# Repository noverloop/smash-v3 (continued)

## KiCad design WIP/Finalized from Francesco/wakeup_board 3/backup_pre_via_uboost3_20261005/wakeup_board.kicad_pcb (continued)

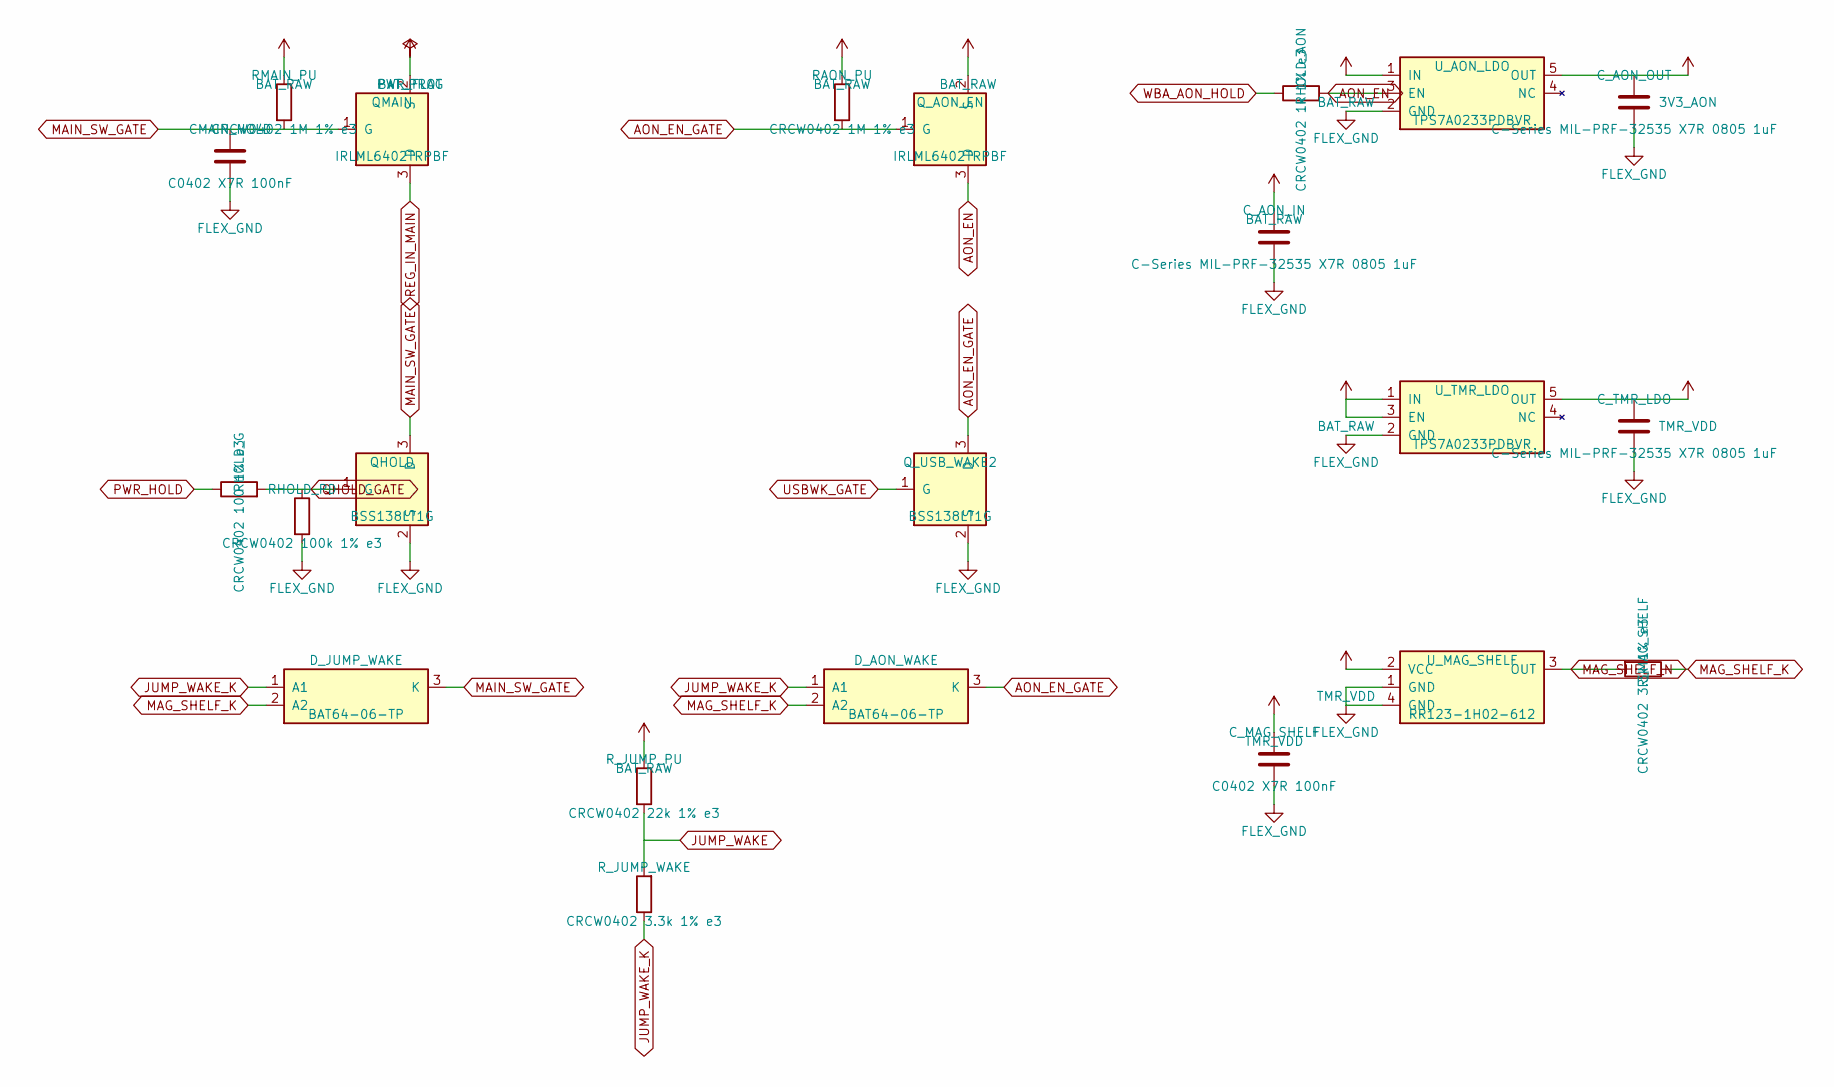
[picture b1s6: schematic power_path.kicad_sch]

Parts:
CMAIN_HOLD: C0402 X7R 100nF; Capacitor_SMD_C_0402_1005Metric
C_AON_IN: C-Series MIL-PRF-32535 X7R 0805 1uF; Capacitor_SMD_C_0805_2012Metric
C_AON_OUT: C-Series MIL-PRF-32535 X7R 0805 1uF; Capacitor_SMD_C_0805_2012Metric
C_MAG_SHELF: C0402 X7R 100nF; Capacitor_SMD_C_0402_1005Metric
C_TMR_LDO: C-Series MIL-PRF-32535 X7R 0805 1uF; Capacitor_SMD_C_0805_2012Metric
D_AON_WAKE: BAT64-06-TP; SOT95P237X125-3N
D_JUMP_WAKE: BAT64-06-TP; SOT95P237X125-3N
QHOLD: BSS138LT1G; SOT96P237X111-3N
QMAIN: IRLML6402TRPBF; SOT95P237X112-3N
Q_AON_EN: IRLML6402TRPBF; SOT95P237X112-3N
Q_USB_WAKE2: BSS138LT1G; SOT96P237X111-3N
RAON_PU: CRCW0402 1M 1% e3; Resistor_SMD_R_0402_1005Metric
RHOLD_AON: CRCW0402 1k 1% e3; Resistor_SMD_R_0402_1005Metric
RHOLD_G: CRCW0402 100 1% e3; Resistor_SMD_R_0402_1005Metric
RHOLD_PD: CRCW0402 100k 1% e3; Resistor_SMD_R_0402_1005Metric
RMAIN_PU: CRCW0402 1M 1% e3; Resistor_SMD_R_0402_1005Metric
R_JUMP_PU: CRCW0402 22k 1% e3; Resistor_SMD_R_0402_1005Metric
R_JUMP_WAKE: CRCW0402 3.3k 1% e3; Resistor_SMD_R_0402_1005Metric
R_MAG_SHELF: CRCW0402 3.3k 1% e3; Resistor_SMD_R_0402_1005Metric
U_AON_LDO: TPS7A0233PDBVR; SOT95P280X145-5N
U_MAG_SHELF: RR123-1H02-612
U_TMR_LDO: TPS7A0233PDBVR; SOT95P280X145-5N

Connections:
3V3_AON: C_AON_OUT.1, U_AON_LDO.5 (OUT); also elsewhere on the board
AON_EN: Q_AON_EN.3 (D), RHOLD_AON.2, U_AON_LDO.3 (EN)
AON_EN_GATE: D_AON_WAKE.3 (K), Q_AON_EN.1 (G), Q_USB_WAKE2.3 (D), RAON_PU.2
BAT_PROT: QMAIN.2 (S); also elsewhere on the board
BAT_RAW: C_AON_IN.1, Q_AON_EN.2 (S), RAON_PU.1, RMAIN_PU.1, R_JUMP_PU.1, U_AON_LDO.1 (IN), U_TMR_LDO.1 (IN), U_TMR_LDO.3 (EN); also elsewhere on the board
FLEX_GND: CMAIN_HOLD.2, C_AON_IN.2, C_AON_OUT.2, C_MAG_SHELF.2, C_TMR_LDO.2, QHOLD.2 (S), Q_USB_WAKE2.2 (S), RHOLD_PD.2, U_AON_LDO.2 (GND), U_MAG_SHELF.1 (GND), U_MAG_SHELF.4 (GND), U_TMR_LDO.2 (GND); also elsewhere on the board
JUMP_WAKE_K: D_AON_WAKE.1 (A1), D_JUMP_WAKE.1 (A1), R_JUMP_WAKE.1
MAG_SHELF_K: D_AON_WAKE.2 (A2), D_JUMP_WAKE.2 (A2), R_MAG_SHELF.1
MAG_SHELF_N: R_MAG_SHELF.2, U_MAG_SHELF.3 (OUT)
MAIN_SW_GATE: CMAIN_HOLD.1, D_JUMP_WAKE.3 (K), QHOLD.3 (D), QMAIN.1 (G), RMAIN_PU.2; also elsewhere on the board
PWR_HOLD: RHOLD_G.1; also elsewhere on the board
QHOLD_GATE: QHOLD.1 (G), RHOLD_G.2, RHOLD_PD.1
REG_IN_MAIN: QMAIN.3 (D); also elsewhere on the board
TMR_VDD: C_MAG_SHELF.1, C_TMR_LDO.1, U_MAG_SHELF.2 (VCC), U_TMR_LDO.5 (OUT)
USBWK_GATE: Q_USB_WAKE2.1 (G); also elsewhere on the board
WBA_AON_HOLD: RHOLD_AON.1; also elsewhere on the board

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
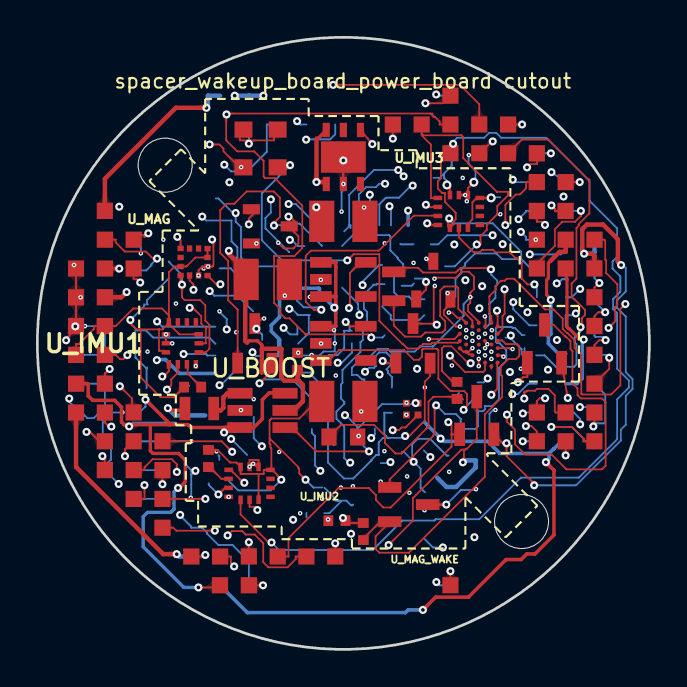
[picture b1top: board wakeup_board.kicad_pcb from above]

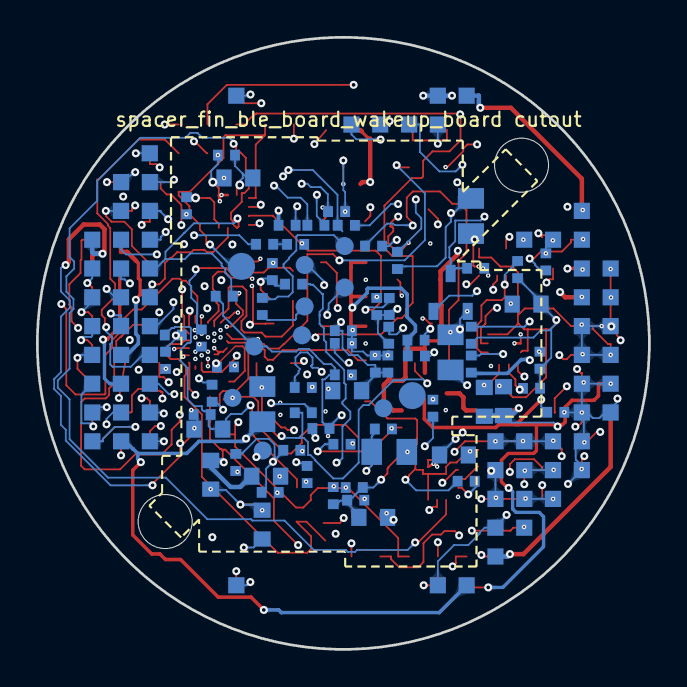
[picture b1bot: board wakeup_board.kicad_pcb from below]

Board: 14 copper layers, 34.0 x 34.0 mm, 111 parts (80 on the bottom side), 85 nets.

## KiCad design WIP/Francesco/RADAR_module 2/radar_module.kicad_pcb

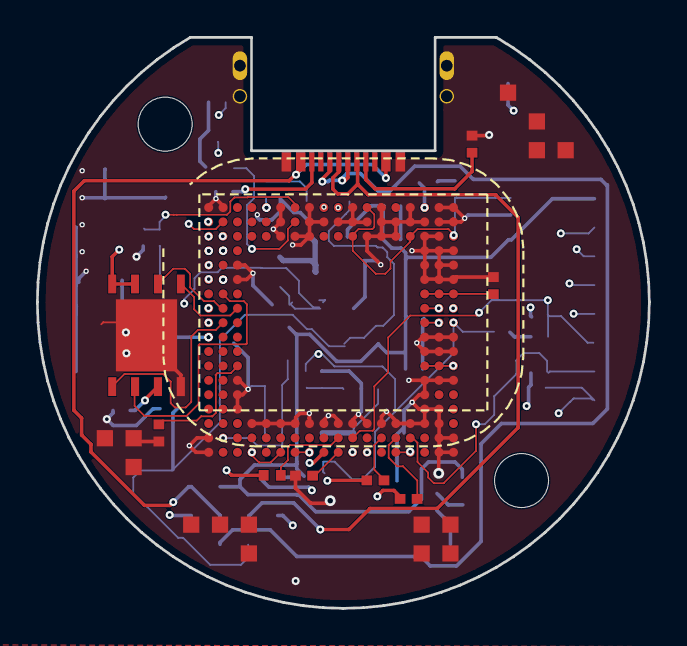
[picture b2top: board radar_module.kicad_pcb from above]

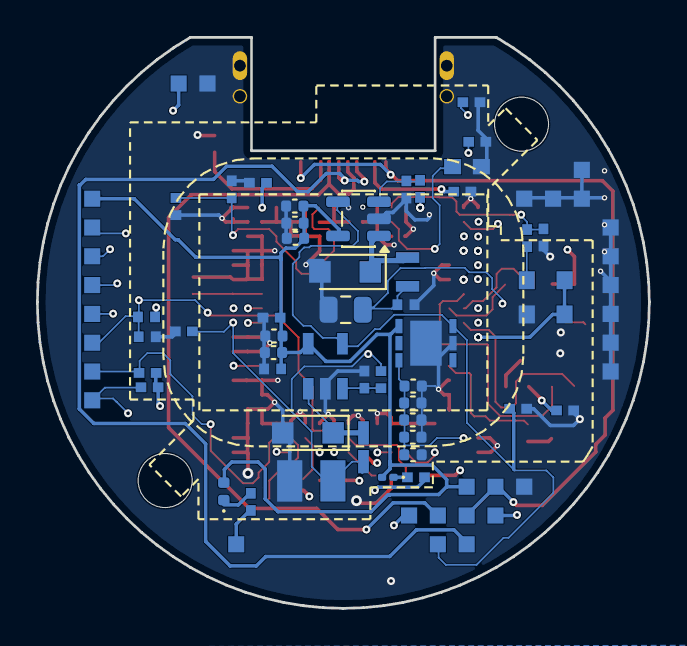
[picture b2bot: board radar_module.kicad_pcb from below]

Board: 20 copper layers, 34.0 x 31.7 mm, 59 parts (48 on the bottom side), 43 nets.

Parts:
C_AWR_1V2_1: T491T 22uF (3528-12 thinnest variant); C_0805_2012Metric
C_AWR_1V2_2, C_AWR_1V3_2, C_AWR_1V8_2, C_AWR_14APLL, C_AWR_14SYNTH: C0402 X7R 100nF; C_0402_1005Metric
C_AWR_1V3_1: T491T 22uF (3528-12 thinnest variant); CP_EIA-3528-12_Kemet-T
C_AWR_1V8_1_1, C_AWR_1V8_1_2, C_AWR_1V8_1_3, C_AWR_1V8_1_4, C_AWR_1V8_1_5: C-Series MIL-PRF-32535 X7R 0603 2.2uF; C_0402_1005Metric
C_AWR_BUCK_IN1_1, C_AWR_BUCK_IN1_2, C_AWR_BUCK_IN1_3, C_AWR_BUCK_IN1_4, C_AWR_BUCK_IN1_5: C-Series MIL-PRF-32535 X7R 0603 2.2uF; C_0402_1005Metric
C_AWR_BUCK_IN2: C0402 X7R 100nF; C_0402_1005Metric
C_AWR_CLKM: SQCSVA 100pF; C_0603_1608Metric
C_AWR_FLASH_VCC: C0402 X7R 100nF; C_0402_1005Metric
C_AWR_NRST: C0402 X7R 100nF; C_0402_1005Metric
C_AWR_OSC_VDD: C0402 X7R 100nF; C_0402_1005Metric
C_AWR_VBGAP: C0402 X7R 100nF; C_0402_1005Metric
C_AWR_VOUT_PA: C0402 X7R 100nF; C_0402_1005Metric
C_NOSE_LED: C0402 X7R 100nF; C_0402_1005Metric
D_AWR_BUCK12, D_AWR_BUCK13: MBRS340T3G; Nexperia_CFP3_SOD-123W
D_NOSE_G: LTST-C190GKT; LED_0402_1005Metric
D_NOSE_R: LTST-C190KRKT; LED_0201_0603Metric
J_USB_C: UJ20-C-H-G-MSMT-1A-P16-TR-67; SAMESKY_UJ20-C-H-G-MSMT-1A-P16-TR-67
J_radar_module_spacer_radar_module_nose_cap: LGA_lands; J_radar_module_spacer_radar_module_nose_cap
L_AWR_BUCK12, L_AWR_BUCK13: TMS201210ALM-2R2MTAA; L_2012_2.0x1.25mm
P_radar_module_spacer_companion_compute_radar_module: LGA_lands; P_radar_module_spacer_companion_compute_radar_module
R_AWR12_FB1, R_AWR12_FB2, R_AWR13_FB2: CRCW0402 100k 1% e3; R_0402_1005Metric
R_AWR13_FB1: CRCW0402 118k 1% e3; R_0402_1005Metric
R_AWR_CLK_SER: CRCW0402 330 1% e3; R_0402_1005Metric
R_AWR_CLK_SH: CRCW0402 390 1% e3; R_0402_1005Metric
R_AWR_DRDY_PU: CRCW0402 10k 1% e3; R_0402_1005Metric
R_AWR_FAULT_PU: CRCW0402 100k 1% e3; R_0402_1005Metric
R_AWR_NERRIN_PU: CRCW0402 10k 1% e3; R_0402_1005Metric
R_AWR_NRST: CRCW0402 10k 1% e3; R_0402_1005Metric
R_AWR_SOP0, R_AWR_SOP1, R_AWR_SOP2: CRCW0402 10k 1% e3; R_0402_1005Metric
R_AWR_WARMRST_PU: CRCW0402 10k 1% e3; R_0402_1005Metric
R_NOSE_LED_G: CRCW0402 330 1% e3; R_0402_1005Metric
R_NOSE_LED_R: CRCW0402 330 1% e3; R_0402_1005Metric
R_RADAR_EN_PD: CRCW0402 100k 1% e3; R_0402_1005Metric
R_USB_CC1, R_USB_CC2: CRCW0402 5.1k 1% e3; R_0402_1005Metric
U_AWR: AWR1843ARBGALPQ1; BGA180C80P18X18_1500X1500X96
U_AWR_BUCK12: LMR10510XMFE/NOPB; SOT-23-5
U_AWR_BUCK13: LMR10510XMFE/NOPB; SOT95P280X145-5N
U_AWR_FLASH: SST26VF080A-104I/MF; SON127P600X500X80-9N-D
U_AWR_LDO18: LDL112PV18R; SON95P300X300X100-7N-D
Y_AWR_HSE: DSC1001CI5-040.0000; DSC1001CI50080000

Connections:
AWR_1V2: C_AWR_1V2_1.1, C_AWR_1V2_2.1, L_AWR_BUCK12.2, R_AWR12_FB1.1, U_AWR.A5, U_AWR.C1, U_AWR.E1, U_AWR.J1, U_AWR.V4, U_AWR.V6, U_AWR.V7, U_AWR.V8, U_AWR.V12, U_AWR.V14, U_AWR.V15
AWR_1V2_FB: R_AWR12_FB1.2, R_AWR12_FB2.1, U_AWR_BUCK12.3
AWR_1V2_SW: D_AWR_BUCK12.1, L_AWR_BUCK12.1, U_AWR_BUCK12.1
AWR_1V3: C_AWR_1V3_1.1, C_AWR_1V3_2.1, L_AWR_BUCK13.2, R_AWR13_FB1.1, U_AWR.H16, U_AWR.H17, U_AWR.H18, U_AWR.J16, U_AWR.J17, U_AWR.J18
AWR_1V3_FB: R_AWR13_FB1.2, R_AWR13_FB2.1, U_AWR_BUCK13.3
AWR_1V3_SW: D_AWR_BUCK13.1, L_AWR_BUCK13.1, U_AWR_BUCK13.1
AWR_1V8: C_AWR_1V8_1_1.1, C_AWR_1V8_1_2.1, C_AWR_1V8_1_3.1, C_AWR_1V8_1_4.1, C_AWR_1V8_1_5.1, C_AWR_1V8_2.1, C_AWR_OSC_VDD.1, U_AWR.A12, U_AWR.B1, U_AWR.C11, U_AWR.C15, U_AWR.C18, U_AWR.F1, U_AWR.K1, U_AWR.M16, U_AWR.M17, U_AWR.M18, U_AWR.U2, U_AWR.V11, U_AWR_LDO18.4, Y_AWR_HSE.1, Y_AWR_HSE.4
AWR_CLKM: C_AWR_CLKM.1, U_AWR.B7
AWR_CLKREF: R_AWR_CLK_SER.2, R_AWR_CLK_SH.1, U_AWR.A7
AWR_DRDY: P_radar_module_spacer_companion_compute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.1, R_AWR_DRDY_PU.2, U_AWR.B2
AWR_FAULT: P_radar_module_spacer_companion_compute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.2, R_AWR_FAULT_PU.2, U_AWR.U15
AWR_NERR_IN: R_AWR_NERRIN_PU.2, U_AWR.U14
AWR_NRESET: C_AWR_NRST.1, P_radar_module_spacer_companion_compute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.3, R_AWR_NRST.2, U_AWR.U11
AWR_OSC_OUT: R_AWR_CLK_SER.1, Y_AWR_HSE.3
AWR_QSPI_CLK: U_AWR.H2, U_AWR_FLASH.6
AWR_QSPI_CS: U_AWR.J2, U_AWR_FLASH.1
AWR_QSPI_SI: U_AWR.H3, U_AWR_FLASH.5
AWR_QSPI_SO: U_AWR.G2, U_AWR_FLASH.2
AWR_SOP0: R_AWR_SOP0.2, U_AWR.U10
AWR_SOP1: R_AWR_SOP1.1, U_AWR.M3
AWR_SOP2: R_AWR_SOP2.1, U_AWR.V10
AWR_SPI_CLK: P_radar_module_spacer_companion_compute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.4, U_AWR.D2
AWR_SPI_CS: P_radar_module_spacer_companion_compute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.5, U_AWR.C2
AWR_SPI_MISO: P_radar_module_spacer_companion_compute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.6, U_AWR.D1
AWR_SPI_MOSI: P_radar_module_spacer_companion_compute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.7, U_AWR.F2
AWR_VOUT_14APLL: C_AWR_14APLL.1, U_AWR.A10
AWR_VOUT_14SYNTH: C_AWR_14SYNTH.1, U_AWR.A9
AWR_VOUT_PA: C_AWR_VOUT_PA.1, U_AWR.G16, U_AWR.G17, U_AWR.G18
AWR_WARM_RST: R_AWR_WARMRST_PU.2, U_AWR.U13
BAT_PROT: C_AWR_BUCK_IN1_1.1, C_AWR_BUCK_IN1_2.1, C_AWR_BUCK_IN1_3.1, C_AWR_BUCK_IN1_4.1, C_AWR_BUCK_IN1_5.1, C_AWR_BUCK_IN2.1, C_NOSE_LED.1, D_NOSE_G.2, D_NOSE_R.2, P_radar_module_spacer_companion_compute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.8, P_radar_module_spacer_companion_compute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.17, U_AWR_BUCK12.5, U_AWR_BUCK13.5, U_AWR_LDO18.6
COMP_3V3: C_AWR_FLASH_VCC.1, P_radar_module_spacer_companion_compute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.9, P_radar_module_spacer_companion_compute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.18, R_AWR_DRDY_PU.1, R_AWR_FAULT_PU.1, R_AWR_NERRIN_PU.1, R_AWR_NRST.1, R_AWR_SOP0.1, R_AWR_WARMRST_PU.1, U_AWR.H1, U_AWR.V9, U_AWR_FLASH.3, U_AWR_FLASH.7, U_AWR_FLASH.8
FLEX_GND: C_AWR_1V2_1.2, C_AWR_1V2_2.2, C_AWR_1V3_1.2, C_AWR_1V3_2.2, C_AWR_1V8_1_1.2, C_AWR_1V8_1_2.2, C_AWR_1V8_1_3.2, C_AWR_1V8_1_4.2, C_AWR_1V8_1_5.2, C_AWR_1V8_2.2, C_AWR_14APLL.2, C_AWR_14SYNTH.2, C_AWR_BUCK_IN1_1.2, C_AWR_BUCK_IN1_2.2, C_AWR_BUCK_IN1_3.2, C_AWR_BUCK_IN1_4.2, C_AWR_BUCK_IN1_5.2, C_AWR_BUCK_IN2.2, C_AWR_CLKM.2, C_AWR_FLASH_VCC.2, C_AWR_NRST.2, C_AWR_OSC_VDD.2, C_AWR_VBGAP.2, C_AWR_VOUT_PA.2, C_NOSE_LED.2, D_AWR_BUCK12.2, D_AWR_BUCK13.2, J_USB_C.A1_B12, J_USB_C.B1_A12, J_USB_C.SH1, J_USB_C.SH2, J_USB_C.SH3, J_USB_C.SH4, J_radar_module_spacer_radar_module_nose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.1, J_radar_module_spacer_radar_module_nose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.2, J_radar_module_spacer_radar_module_nose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.3, J_radar_module_spacer_radar_module_nose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.4, J_radar_module_spacer_radar_module_nose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.5, J_radar_module_spacer_radar_module_nose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.6, J_radar_module_spacer_radar_module_nose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.7, J_radar_module_spacer_radar_module_nose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.8, J_radar_module_spacer_radar_module_nose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.9, J_radar_module_spacer_radar_module_nose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.10, J_radar_module_spacer_radar_module_nose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.11, J_radar_module_spacer_radar_module_nose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.12, J_radar_module_spacer_radar_module_nose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.13, J_radar_module_spacer_radar_module_nose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.14, J_radar_module_spacer_radar_module_nose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.15, P_radar_module_spacer_companion_compute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.10, P_radar_module_spacer_companion_compute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.20, P_radar_module_spacer_companion_compute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.21, P_radar_module_spacer_companion_compute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.22, P_radar_module_spacer_companion_compute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.23, P_radar_module_spacer_companion_compute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.24, P_radar_module_spacer_companion_compute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.25, P_radar_module_spacer_companion_compute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.26, P_radar_module_spacer_companion_compute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.27, P_radar_module_spacer_companion_compute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.28, P_radar_module_spacer_companion_compute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.29, P_radar_module_spacer_companion_compute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.30, R_AWR12_FB2.2, R_AWR13_FB2.2, R_AWR_CLK_SH.2, R_AWR_SOP1.2, R_AWR_SOP2.2, R_RADAR_EN_PD.2, R_USB_CC1.2, R_USB_CC2.2, U_AWR.A1, U_AWR.A2, U_AWR.A6, U_AWR.A8, U_AWR.A11, U_AWR.A13, U_AWR.A15, U_AWR.A17, U_AWR.A18, U_AWR.B6, U_AWR.B8, U_AWR.B9, U_AWR.B10, U_AWR.B11, U_AWR.B12, U_AWR.B13, U_AWR.B14, U_AWR.B15, U_AWR.B16, U_AWR.B17, U_AWR.B18, U_AWR.C6, U_AWR.C7, U_AWR.C8, U_AWR.C12, U_AWR.C13, U_AWR.C14, U_AWR.C16, U_AWR.C17, U_AWR.D16, U_AWR.D17, U_AWR.D18, U_AWR.E3, U_AWR.E16, U_AWR.E17, U_AWR.E18, U_AWR.F3, U_AWR.F16, U_AWR.F17, U_AWR.F18, U_AWR.K16, U_AWR.K17, U_AWR.K18, U_AWR.L16, U_AWR.L17, U_AWR.L18, U_AWR.N3, U_AWR.N16, U_AWR.N17, U_AWR.N18, U_AWR.P3, U_AWR.P16, U_AWR.R3, U_AWR.R16, U_AWR.R17, U_AWR.T4, U_AWR.T5, U_AWR.T6, U_AWR.T7, U_AWR.T8, U_AWR.T9, U_AWR.T10, U_AWR.T11, U_AWR.T12, U_AWR.T13, U_AWR.T14, U_AWR.T15, U_AWR.T16, U_AWR.T17, U_AWR.U1, U_AWR.U17, U_AWR.U18, U_AWR.V1, U_AWR.V17, U_AWR.V18, U_AWR_BUCK12.2, U_AWR_BUCK13.2, U_AWR_FLASH.4, U_AWR_FLASH.9, U_AWR_LDO18.2, U_AWR_LDO18.7, Y_AWR_HSE.2
NOSE_LED_G: P_radar_module_spacer_companion_compute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.11, R_NOSE_LED_G.2
NOSE_LED_G_K: D_NOSE_G.1, R_NOSE_LED_G.1
NOSE_LED_R: P_radar_module_spacer_companion_compute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.12, R_NOSE_LED_R.2
NOSE_LED_R_K: D_NOSE_R.1, R_NOSE_LED_R.1
RADAR_EN: P_radar_module_spacer_companion_compute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.13, R_RADAR_EN_PD.1, U_AWR_BUCK12.4, U_AWR_BUCK13.4, U_AWR_LDO18.1
USB_CC1: J_USB_C.A5, R_USB_CC1.1
USB_CC2: J_USB_C.B5, R_USB_CC2.1
USB_DM: J_USB_C.A7, J_USB_C.B7, P_radar_module_spacer_companion_compute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.14
USB_DP: J_USB_C.A6, J_USB_C.B6, P_radar_module_spacer_companion_compute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.15
USB_VBUS: J_USB_C.A4_B9, J_USB_C.B4_A9, P_radar_module_spacer_companion_compute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.16, P_radar_module_spacer_companion_compute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.19
VBGAP: C_AWR_VBGAP.1, U_AWR.A16

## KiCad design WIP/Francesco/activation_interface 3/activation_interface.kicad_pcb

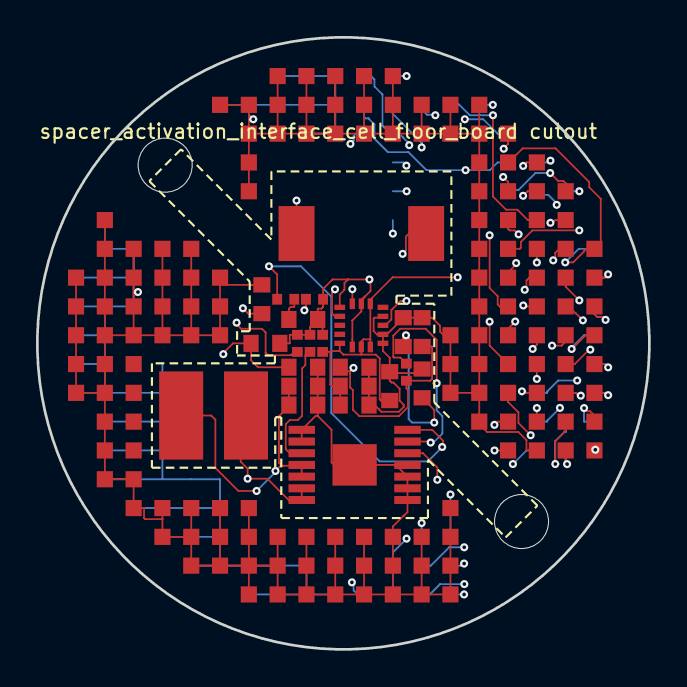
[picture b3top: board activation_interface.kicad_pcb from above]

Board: 14 copper layers, 34.0 x 34.0 mm, 25 parts (1 on the bottom side), 42 nets.

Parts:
C_FIRE_COMP: C-Series MIL-PRF-32535 X7R 0603 220nF; Capacitor_SMD_C_0603_1608Metric
C_FIRE_IN_1, C_FIRE_IN_2, C_FIRE_IN_3, C_FIRE_IN_4, C_FIRE_IN_5: C-Series MIL-PRF-32535 X7R 0603 2.2uF; Capacitor_SMD_C_0603_1608Metric
C_FIRE_OUT_1, C_FIRE_OUT_2: C-Series MIL-PRF-32535 X7R 0603 2.2uF; Capacitor_SMD_C_0603_1608Metric
C_FIRE_SS: C0402 X7R 47nF; Capacitor_SMD_C_0402_1005Metric
C_HACC1: C0402 X7R 100nF; Capacitor_SMD_C_0402_1005Metric
C_HACC2_1, C_HACC2_2, C_HACC2_3, C_HACC2_4, C_HACC2_5: C-Series MIL-PRF-32535 X7R 0603 2.2uF; Capacitor_SMD_C_0603_1608Metric
D_FIRE: MBRS540T3G; DIOM7958X256N
J_activation_interface_spacer_activation_interface_cell_floor_board: LGA_lands; J_activation_interface_spacer_activation_interface_cell_flo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
L_FIRE: 744043100; INDPM4848X280N
P_activation_interface_spacer_aft_end_board_activation_interface: LGA_lands; P_activation_interface_spacer_aft_end_board_activation_inte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
R_FIRE_COMP: CRCW0402 1.6k 1% e3; Resistor_SMD_R_0402_1005Metric
R_FIRE_FB1: CRCW0402 261k 1% e3; Resistor_SMD_R_0402_1005Metric
R_FIRE_FB2: CRCW0402 10k 1% e3; Resistor_SMD_R_0402_1005Metric
R_FIRE_FREQ: CRCW0402 176k 1% e3; Resistor_SMD_R_0402_1005Metric
U_FIRE_BOOST: TPS61175PWPR; SOP65P640X120-15N
U_HACC: H3LIS331DLTR; LIS3DHTR (LGA-16)

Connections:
3V3: C_HACC1.1, C_HACC2_1.1, C_HACC2_2.1, C_HACC2_3.1, C_HACC2_4.1, C_HACC2_5.1, J_activation_interface_spacer_activatio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.1, J_activation_interface_spacer_activatio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.36, J_activation_interface_spacer_activatio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.41, P_activation_interface_spacer_aft_end_b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.1, P_activation_interface_spacer_aft_end_b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.34, P_activation_interface_spacer_aft_end_b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.40, U_HACC.1, U_HACC.8, U_HACC.14, U_HACC.15
3V3_AON: J_activation_interface_spacer_activatio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.2, J_activation_interface_spacer_activatio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.37, P_activation_interface_spacer_aft_end_b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.2, P_activation_interface_spacer_aft_end_b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.35
ACTIVATE_CONFIRM: J_activation_interface_spacer_activatio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.3, P_activation_interface_spacer_aft_end_b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.3
ACTIVATE_SET: J_activation_interface_spacer_activatio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.4, P_activation_interface_spacer_aft_end_b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.4
BAT_PROT: J_activation_interface_spacer_activatio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.5, J_activation_interface_spacer_activatio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.38, P_activation_interface_spacer_aft_end_b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.5, P_activation_interface_spacer_aft_end_b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.36
BAT_RAW: J_activation_interface_spacer_activatio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.6, J_activation_interface_spacer_activatio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.39, P_activation_interface_spacer_aft_end_b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.6, P_activation_interface_spacer_aft_end_b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.37
BOOT0: J_activation_interface_spacer_activatio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.7, P_activation_interface_spacer_aft_end_b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.7
COMP_5V: C_FIRE_IN_1.1, C_FIRE_IN_2.1, C_FIRE_IN_3.1, C_FIRE_IN_4.1, C_FIRE_IN_5.1, J_activation_interface_spacer_activatio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.8, J_activation_interface_spacer_activatio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.40, L_FIRE.1, P_activation_interface_spacer_aft_end_b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.8, P_activation_interface_spacer_aft_end_b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.38, U_FIRE_BOOST.3, U_FIRE_BOOST.4
COMP_SWDCLK: J_activation_interface_spacer_activatio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.9, P_activation_interface_spacer_aft_end_b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.9
COMP_SWDIO: J_activation_interface_spacer_activatio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.10, P_activation_interface_spacer_aft_end_b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.10
EXT_CAN_RX: J_activation_interface_spacer_activatio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.11, P_activation_interface_spacer_aft_end_b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.11
EXT_CAN_TX: J_activation_interface_spacer_activatio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.12, P_activation_interface_spacer_aft_end_b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.12
FIN1_AOUT1: J_activation_interface_spacer_activatio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.13, P_activation_interface_spacer_aft_end_b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.13
FIN2_AOUT1: J_activation_interface_spacer_activatio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.14, P_activation_interface_spacer_aft_end_b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.14
FIN3_AOUT1: J_activation_interface_spacer_activatio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.15, P_activation_interface_spacer_aft_end_b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.15
FIN4_AOUT1: J_activation_interface_spacer_activatio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.16, P_activation_interface_spacer_aft_end_b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.16
FIN_HALL: J_activation_interface_spacer_activatio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.17, P_activation_interface_spacer_aft_end_b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.17
FIN_VREF: J_activation_interface_spacer_activatio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.18, P_activation_interface_spacer_aft_end_b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.18
FIRE_COMP: R_FIRE_COMP.1, U_FIRE_BOOST.8
FIRE_COMP_C: C_FIRE_COMP.1, R_FIRE_COMP.2
FIRE_FB: R_FIRE_FB1.2, R_FIRE_FB2.1, U_FIRE_BOOST.9
FIRE_FREQ: R_FIRE_FREQ.1, U_FIRE_BOOST.10
FIRE_HV: C_FIRE_OUT_1.1, C_FIRE_OUT_2.1, D_FIRE.1, P_activation_interface_spacer_aft_end_b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.19, P_activation_interface_spacer_aft_end_b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.39, R_FIRE_FB1.1
FIRE_SS: C_FIRE_SS.1, U_FIRE_BOOST.5
FIRE_SW: D_FIRE.2, L_FIRE.2, U_FIRE_BOOST.1, U_FIRE_BOOST.2
FLEX_GND: C_FIRE_COMP.2, C_FIRE_IN_1.2, C_FIRE_IN_2.2, C_FIRE_IN_3.2, C_FIRE_IN_4.2, C_FIRE_IN_5.2, C_FIRE_OUT_1.2, C_FIRE_OUT_2.2, C_FIRE_SS.2, C_HACC1.2, C_HACC2_1.2, C_HACC2_2.2, C_HACC2_3.2, C_HACC2_4.2, C_HACC2_5.2, J_activation_interface_spacer_activatio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.19, J_activation_interface_spacer_activatio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.42, J_activation_interface_spacer_activatio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.43, J_activation_interface_spacer_activatio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.44, J_activation_interface_spacer_activatio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.45, J_activation_interface_spacer_activatio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.46, J_activation_interface_spacer_activatio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.47, J_activation_interface_spacer_activatio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.48, J_activation_interface_spacer_activatio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.49, J_activation_interface_spacer_activatio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.50, J_activation_interface_spacer_activatio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.51, J_activation_interface_spacer_activatio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.52, J_activation_interface_spacer_activatio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.53, J_activation_interface_spacer_activatio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.54, J_activation_interface_spacer_activatio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.55, J_activation_interface_spacer_activatio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.56, J_activation_interface_spacer_activatio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.57, J_activation_interface_spacer_activatio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.58, J_activation_interface_spacer_activatio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.59, J_activation_interface_spacer_activatio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.60, J_activation_interface_spacer_activatio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.61, J_activation_interface_spacer_activatio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.62, J_activation_interface_spacer_activatio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.63, J_activation_interface_spacer_activatio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.64, J_activation_interface_spacer_activatio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.65, J_activation_interface_spacer_activatio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.66, J_activation_interface_spacer_activatio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.67, J_activation_interface_spacer_activatio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.68, J_activation_interface_spacer_activatio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.69, J_activation_interface_spacer_activatio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.70, J_activation_interface_spacer_activatio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.71, J_activation_interface_spacer_activatio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.72, J_activation_interface_spacer_activatio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.73, J_activation_interface_spacer_activatio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.74, J_activation_interface_spacer_activatio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.75, J_activation_interface_spacer_activatio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.76, J_activation_interface_spacer_activatio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.77, J_activation_interface_spacer_activatio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.78, J_activation_interface_spacer_activatio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.79, J_activation_interface_spacer_activatio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.80, J_activation_interface_spacer_activatio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.81, J_activation_interface_spacer_activatio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.82, J_activation_interface_spacer_activatio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.83, J_activation_interface_spacer_activatio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.84, J_activation_interface_spacer_activatio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.85, J_activation_interface_spacer_activatio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.86, J_activation_interface_spacer_activatio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.87, J_activation_interface_spacer_activatio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.88, J_activation_interface_spacer_activatio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.89, J_activation_interface_spacer_activatio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.90, J_activation_interface_spacer_activatio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.91, J_activation_interface_spacer_activatio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.92, J_activation_interface_spacer_activatio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.93, J_activation_interface_spacer_activatio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.94, J_activation_interface_spacer_activatio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.95, J_activation_interface_spacer_activatio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.96, J_activation_interface_spacer_activatio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.97, J_activation_interface_spacer_activatio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.98, J_activation_interface_spacer_activatio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.99, J_activation_interface_spacer_activatio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.100, J_activation_interface_spacer_activatio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.101, J_activation_interface_spacer_activatio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.102, J_activation_interface_spacer_activatio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.103, J_activation_interface_spacer_activatio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.104, J_activation_interface_spacer_activatio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.105, J_activation_interface_spacer_activatio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.106, J_activation_interface_spacer_activatio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.107, J_activation_interface_spacer_activatio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.108, J_activation_interface_spacer_activatio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.109, J_activation_interface_spacer_activatio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.110, J_activation_interface_spacer_activatio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.111, J_activation_interface_spacer_activatio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.112, J_activation_interface_spacer_activatio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.113, J_activation_interface_spacer_activatio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.114, J_activation_interface_spacer_activatio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.115, J_activation_interface_spacer_activatio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.116, J_activation_interface_spacer_activatio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.117, J_activation_interface_spacer_activatio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.118, J_activation_interface_spacer_activatio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.119, J_activation_interface_spacer_activatio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.120, J_activation_interface_spacer_activatio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.121, J_activation_interface_spacer_activatio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.122, J_activation_interface_spacer_activatio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.123, J_activation_interface_spacer_activatio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.124, J_activation_interface_spacer_activatio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.125, J_activation_interface_spacer_activatio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.126, J_activation_interface_spacer_activatio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.127, J_activation_interface_spacer_activatio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.128, J_activation_interface_spacer_activatio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.129, J_activation_interface_spacer_activatio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.130, J_activation_interface_spacer_activatio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.131, J_activation_interface_spacer_activatio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.132, J_activation_interface_spacer_activatio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.133, J_activation_interface_spacer_activatio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.134, J_activation_interface_spacer_activatio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.135, J_activation_interface_spacer_activatio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.136, J_activation_interface_spacer_activatio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.137, J_activation_interface_spacer_activatio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.138, J_activation_interface_spacer_activatio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.139, J_activation_interface_spacer_activatio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.140, J_activation_interface_spacer_activatio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.141, J_activation_interface_spacer_activatio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.142, J_activation_interface_spacer_activatio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.143, J_activation_interface_spacer_activatio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.144, J_activation_interface_spacer_activatio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.145, J_activation_interface_spacer_activatio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.146, J_activation_interface_spacer_activatio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.147, J_activation_interface_spacer_activatio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.148, J_activation_interface_spacer_activatio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.149, J_activation_interface_spacer_activatio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.150, P_activation_interface_spacer_aft_end_b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.20, P_activation_interface_spacer_aft_end_b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.41, P_activation_interface_spacer_aft_end_b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.42, P_activation_interface_spacer_aft_end_b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.43, P_activation_interface_spacer_aft_end_b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.44, P_activation_interface_spacer_aft_end_b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.45, P_activation_interface_spacer_aft_end_b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.46, P_activation_interface_spacer_aft_end_b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.47, P_activation_interface_spacer_aft_end_b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.48, P_activation_interface_spacer_aft_end_b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.49, P_activation_interface_spacer_aft_end_b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.50, P_activation_interface_spacer_aft_end_b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.51, P_activation_interface_spacer_aft_end_b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.52, P_activation_interface_spacer_aft_end_b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.53, P_activation_interface_spacer_aft_end_b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.54, P_activation_interface_spacer_aft_end_b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.55, P_activation_interface_spacer_aft_end_b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.56, P_activation_interface_spacer_aft_end_b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.57, P_activation_interface_spacer_aft_end_b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.58, P_activation_interface_spacer_aft_end_b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.59, P_activation_interface_spacer_aft_end_b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.60, P_activation_interface_spacer_aft_end_b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.61, P_activation_interface_spacer_aft_end_b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.62, P_activation_interface_spacer_aft_end_b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.63, P_activation_interface_spacer_aft_end_b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.64, P_activation_interface_spacer_aft_end_b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.65, P_activation_interface_spacer_aft_end_b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.66, P_activation_interface_spacer_aft_end_b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.67, P_activation_interface_spacer_aft_end_b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.68, P_activation_interface_spacer_aft_end_b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.69, P_activation_interface_spacer_aft_end_b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.70, P_activation_interface_spacer_aft_end_b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.71, P_activation_interface_spacer_aft_end_b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.72, P_activation_interface_spacer_aft_end_b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.73, P_activation_interface_spacer_aft_end_b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.74, P_activation_interface_spacer_aft_end_b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.75, P_activation_interface_spacer_aft_end_b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.76, P_activation_interface_spacer_aft_end_b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.77, P_activation_interface_spacer_aft_end_b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.78, P_activation_interface_spacer_aft_end_b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.79, P_activation_interface_spacer_aft_end_b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.80, P_activation_interface_spacer_aft_end_b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.81, P_activation_interface_spacer_aft_end_b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.82, P_activation_interface_spacer_aft_end_b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.83, P_activation_interface_spacer_aft_end_b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.84, P_activation_interface_spacer_aft_end_b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.85, P_activation_interface_spacer_aft_end_b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.86, P_activation_interface_spacer_aft_end_b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.87, P_activation_interface_spacer_aft_end_b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.88, P_activation_interface_spacer_aft_end_b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.89, P_activation_interface_spacer_aft_end_b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.90, P_activation_interface_spacer_aft_end_b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.91, P_activation_interface_spacer_aft_end_b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.92, P_activation_interface_spacer_aft_end_b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.93, P_activation_interface_spacer_aft_end_b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.94, P_activation_interface_spacer_aft_end_b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.95, P_activation_interface_spacer_aft_end_b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.96, P_activation_interface_spacer_aft_end_b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.97, P_activation_interface_spacer_aft_end_b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.98, R_FIRE_FB2.2, R_FIRE_FREQ.2, U_FIRE_BOOST.6, U_FIRE_BOOST.7, U_FIRE_BOOST.11, U_FIRE_BOOST.12, U_FIRE_BOOST.13, U_FIRE_BOOST.14, U_FIRE_BOOST.15, U_HACC.5, U_HACC.7, U_HACC.10, U_HACC.12, U_HACC.13, U_HACC.16
GPIO_EXT_0: J_activation_interface_spacer_activatio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.20, P_activation_interface_spacer_aft_end_b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.21
GPIO_EXT_1: J_activation_interface_spacer_activatio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.21, P_activation_interface_spacer_aft_end_b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.22
GPIO_EXT_2: J_activation_interface_spacer_activatio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.22, P_activation_interface_spacer_aft_end_b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.23
GPIO_EXT_3: J_activation_interface_spacer_activatio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.23, P_activation_interface_spacer_aft_end_b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.24
H3LIS_INT1: J_activation_interface_spacer_activatio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.24, U_HACC.11
I2C3_SCL: J_activation_interface_spacer_activatio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.25, U_HACC.4
I2C3_SDA: J_activation_interface_spacer_activatio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.26, U_HACC.6
JUMP_WAKE: J_activation_interface_spacer_activatio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.27, P_activation_interface_spacer_aft_end_b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.25
NRST: J_activation_interface_spacer_activatio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.28, P_activation_interface_spacer_aft_end_b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.26
SWO: J_activation_interface_spacer_activatio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.29, P_activation_interface_spacer_aft_end_b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.27
SYS_I2C_SCL: J_activation_interface_spacer_activatio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.30, P_activation_interface_spacer_aft_end_b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.28
SYS_I2C_SDA: J_activation_interface_spacer_activatio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.31, P_activation_interface_spacer_aft_end_b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.29
SYS_SPI_CS_FIN: J_activation_interface_spacer_activatio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.32, P_activation_interface_spacer_aft_end_b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.30
SYS_SPI_MISO: J_activation_interface_spacer_activatio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.33, P_activation_interface_spacer_aft_end_b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.31
SYS_SPI_MOSI: J_activation_interface_spacer_activatio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.34, P_activation_interface_spacer_aft_end_b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.32
SYS_SPI_SCLK: J_activation_interface_spacer_activatio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.35, P_activation_interface_spacer_aft_end_b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.33
